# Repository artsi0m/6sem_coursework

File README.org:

* Курсовой шестого семестра
Программное обеспечение моделирования физических процессов,
протекающих в системе тестирования сервоприводов квадрокоптера на микроконтроллере ATmega328P

** Используемые программы

| Программа             | Что в ней было произведено                                         |
| Altium Designer       | Схема электрическая принципиальная, экспорт модели из кикада в IDF |
| KiCAD 8               | Схема электрическая принципальная, модель печатной платы           |
| Solidworks Simulation | Импорт IDF из Altium, физические симуляции и экспорт в STEP        |
| COMSOL, ANSYS         | Физические симуляции                                               |

** Используемые классы [xe]latex

| Класс | Документ                                                          |
| xesel | Перечень элементов                                                |
| eskdx | Класс взятый за основу класса bsuir-std для пояснительной записки |

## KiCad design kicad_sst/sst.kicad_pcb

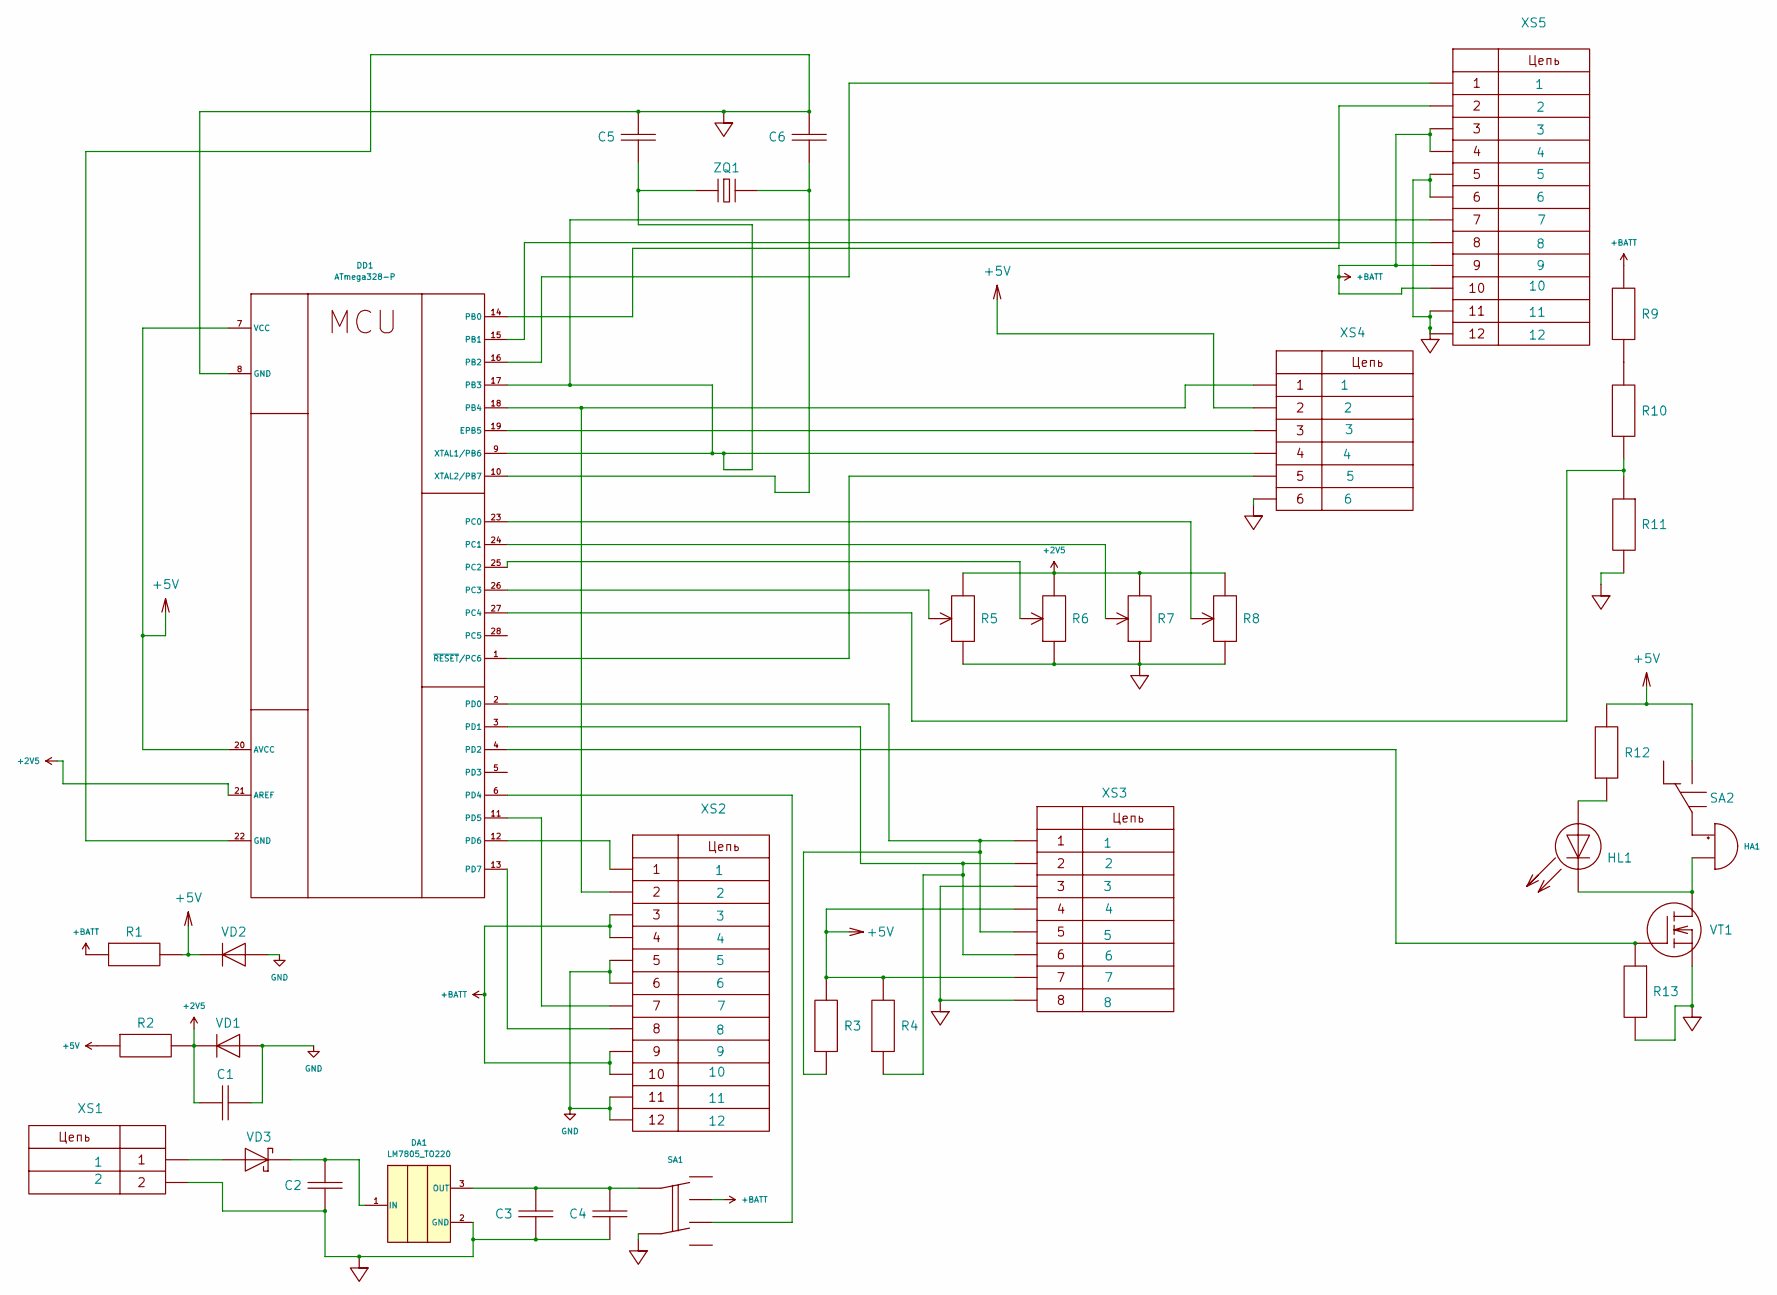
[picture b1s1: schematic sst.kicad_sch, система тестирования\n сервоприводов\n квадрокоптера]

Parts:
C1, C4: C; CP_Radial_D8.0mm_P2.50mm
C2: C; CP_Radial_D8.0mm_P3.50mm
C3: C; CP_Radial_D5.0mm_P2.00mm
C5, C6: C; C_Radial_D6.3mm_H5.0mm_P2.50mm
DA1: LM7805_TO220; TO-220-3_Vertical
DD1: ATmega328-P; DIP-28_W7.62mm
HA1: Buzzer; Buzzer_TDK_PS1240P02BT_D12.2mm_H6.5mm
HL1: HL_LED; LED_D3.0mm
R1, R2, R3, R4, R9, R10, R11, R12, R13: R; R_Axial_DIN0207_L6.3mm_D2.5mm_P7.62mm_Horizontal
R5, R6, R7, R8: R_POT; Potentiometer_TT_P0915N
SA1: SW_CK_JS202011CQN_DPDT_Straight
SA2: SA_SPDT; SW_Slide_SPDT_Angled_CK_OS102011MA1Q
VD1, VD2: VD; D_5KPW_P12.70mm_Horizontal
VD3: VD_Schottky; D_5KPW_P12.70mm_Horizontal
VT1: 2П7240; TO-92
XS1: CONN_2; BarrelJack_SwitchcraftConxall_RAPC10U_Horizontal
XS2, XS5: CONN_12; PinHeader_2x06_P2.54mm_Vertical
XS3: CONN_8; PinSocket_2x04_P2.54mm_Vertical
XS4: CONN_6; PinHeader_2x03_P2.54mm_Vertical
ZQ1: ZQ_CRYSTAL; Crystal_HC49-U_Vertical

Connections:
+2V5: C1.1, DD1.21 (AREF), R2.2, R5.3, R6.3, R7.3, R8.3, VD1.1 (K)
+5V: DD1.7 (VCC), DD1.20 (AVCC), R1.2, R2.1, R3.2, R4.2, R12.2, SA2.2, VD2.1 (K), XS3.4, XS3.7, XS4.2
+BATT: R1.1, R9.2, SA1.4, XS2.3, XS2.4, XS2.9, XS2.10, XS5.3, XS5.4, XS5.9, XS5.10
GND: C1.2, C2.2, C3.2, C4.2, C5.1, C6.1, DA1.2 (GND), DD1.8 (GND), DD1.22 (GND), R5.1, R6.1, R7.1, R8.1, R11.2, R13.2, SA1.2, VD1.2 (A), VD2.2 (A), VT1.1 (S1), XS1.2, XS2.5, XS2.6, XS2.11, XS2.12, XS3.3, XS3.8, XS4.6, XS5.5, XS5.6, XS5.11, XS5.12
unnamed: C2.1, DA1.1 (IN), VD3.1 (K)
unnamed: C3.1, C4.1, DA1.3 (OUT), SA1.1
unnamed: DD1.19 (EPB5), XS4.3
unnamed: DD1.14 (PB0), XS5.2
unnamed: DD1.15 (PB1), XS5.8
unnamed: DD1.16 (PB2), XS5.1
unnamed: C5.2, DD1.9 (XTAL1/PB6), DD1.17 (PB3), XS4.4, XS5.7, ZQ1.1
unnamed: DD1.18 (PB4), XS2.2, XS4.1
unnamed: DD1.23 (PC0), R8.2
unnamed: DD1.24 (PC1), R7.2
unnamed: DD1.25 (PC2), R6.2
unnamed: DD1.26 (PC3), R5.2
unnamed: DD1.27 (PC4), R10.1, R11.1
unnamed: DD1.2 (PD0), R3.1, XS3.1, XS3.5
unnamed: DD1.3 (PD1), R4.1, XS3.2, XS3.6
unnamed: DD1.4 (PD2), R13.1, VT1.2 (G1)
unnamed: DD1.6 (PD4), SA1.5
unnamed: DD1.11 (PD5), XS2.7
unnamed: DD1.12 (PD6), XS2.1
unnamed: DD1.13 (PD7), XS2.8
unnamed: C6.2, DD1.10 (XTAL2/PB7), ZQ1.2
unnamed: DD1.1 (~RESET/PC6), XS4.5
unnamed: HA1.1 (+), SA2.1
unnamed: HA1.2 (-), HL1.1 (K), VT1.3 (D1)
unnamed: HL1.2 (A), R12.1
unnamed: R9.1, R10.2
unnamed: VD3.2 (A), XS1.1

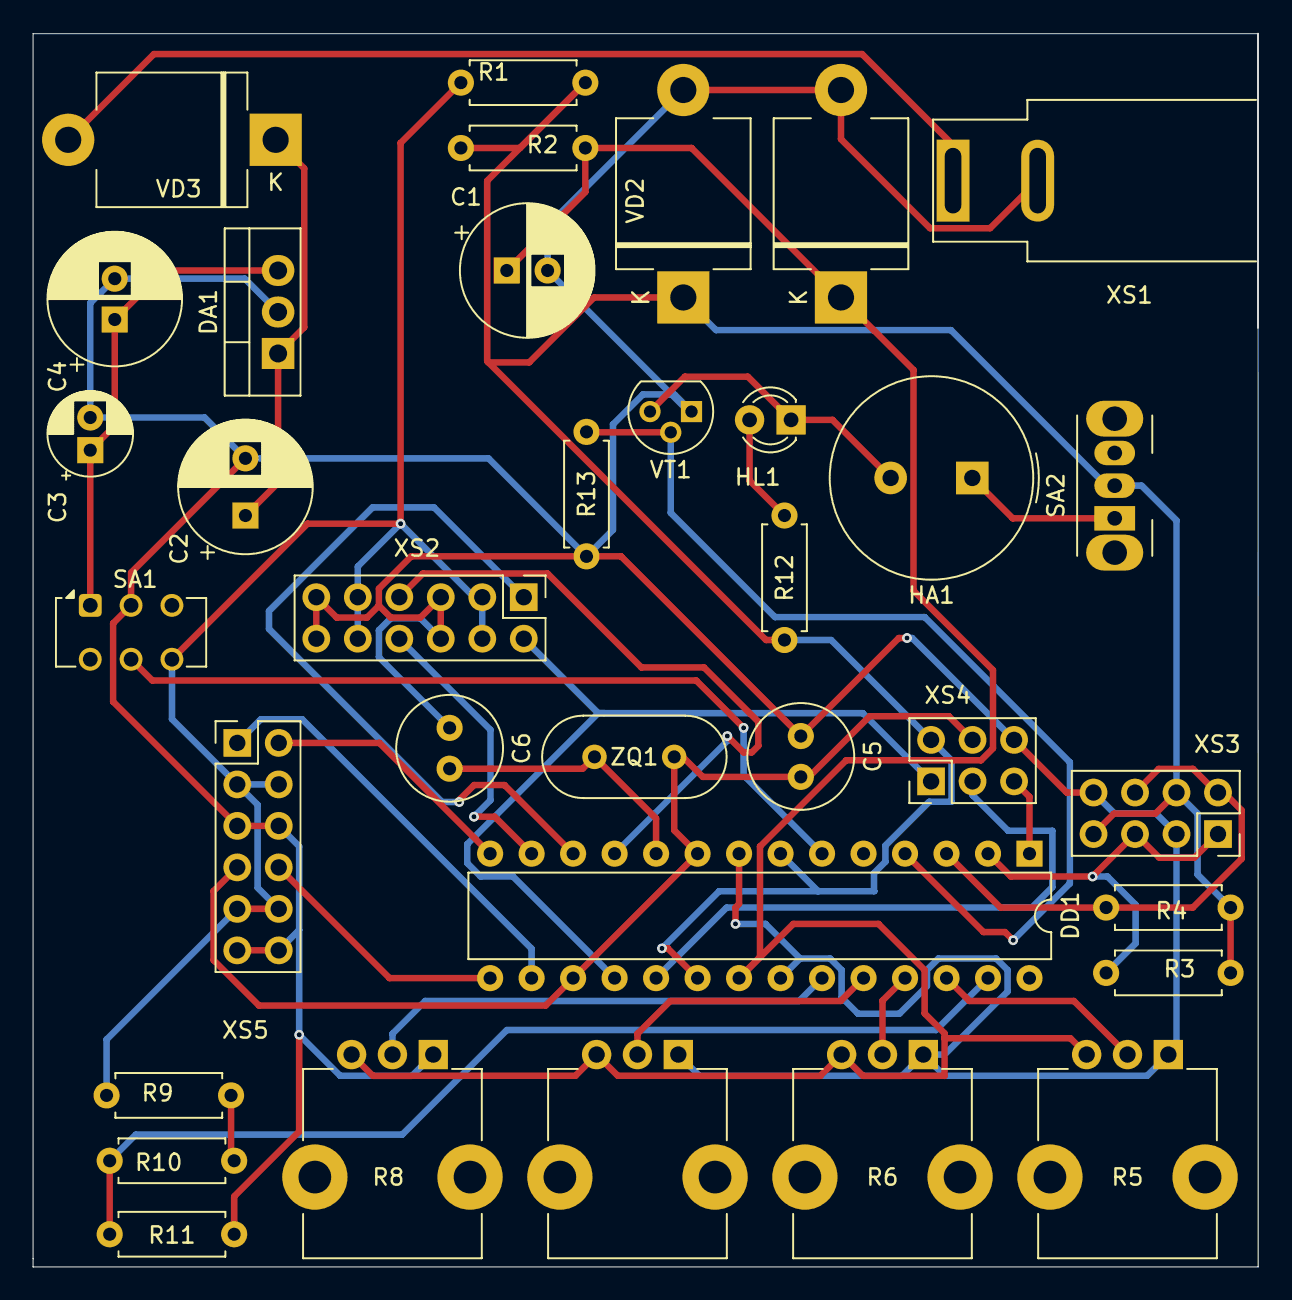
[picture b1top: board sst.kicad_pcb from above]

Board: 2 copper layers, 75.0 x 75.5 mm, 35 parts (0 on the bottom side), 31 nets.

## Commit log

2024-02-29 Первая версия перечня элементов
2024-02-29 Шрифт Open GOST A для чертежей
2024-02-29 README с инфой по используемуму софту
2024-03-01 Мой класс с прошлого курсового
2024-03-01 Начало пояснительной записки, дали 5%
2024-03-15 Initial commit with Altium Project, created schematic lib
2024-03-15 2023-03-15-2115 Readme update
2024-03-15 ЕСКД Класс на схеме электрической принципальной
2024-03-15 SST — Super Servo Tester
2024-03-24 Xtal now has QX designator like in GOST
2024-03-24 Укрупнил микроконтроллер и поменял местами его выводы
2024-03-24 Разместил на схеме микроконтроллер и кварцевый резонатор
2024-03-24 Поставил регулятор напряжения на принципальную схему
2024-03-24 rename ZX to ZQ on Xtal
2024-03-25 Changed LED and MOSFET
2024-03-25 Added connector for 6,8,12 pins
2024-03-25 Updated potentiometr
2024-03-26 All work done on schematics yesterday 2024-03-25
2024-03-26 Placed almost everything on the scheme
2024-03-26 Enumerated all components and changed GND
2024-03-26 Enumerate all elements in project
2024-03-26 Enumerated and connected all
2024-03-26 Fixed connection between XS3 and MCU
2024-03-26 Commit to keep changes in scheme
2024-03-26 Добавил на принципальную схему те части, которые не соеденены с микроконтроллером, пронумеровал всё
2024-03-29 Сменил форму рамки ЕСКд на 2А
2024-03-29 Переместил землю так, чтобы её УГОшка была направлена вниз
2024-03-29 Удалил надпись GND с земли
2024-03-29 Поменял обозначения питания
2024-04-21 Started adding titles to MCU pins
2024-04-24 Created kicad project
2024-04-24 Добавил рамки по госту
2024-04-25 Switched to gost font and set to metric
2024-04-25 Добавил в свою библиотеку из встроенной символ атмеги
2024-04-26 Сделал УГО микроконтроллера по ГОСТ
2024-04-27 Сделал УГО микроконтроллера
2024-04-27 HA УГО
2024-04-27 SA, XS, ZQ added
2024-04-27 Вроде как полная схемная библиотека
2024-04-28 Almsost done with the sceme: part that connected to MCU is connected
2024-04-28 Done with schematic
2024-04-28 Fixes to the schematics
2024-04-28 placed footprints
2024-04-29 Сделлал аннотацию схемы
2024-04-29 Linked footprints to schematics
2024-04-29 Fixes transistor
2024-04-30 Changed couple of footprints for XS
2024-05-01 first try at tracing, and I think I set wrong component at XS4
2024-05-01 Changed footprint for XS4
2024-05-01 version of PCB layout without errors
2024-05-01 pcb without warnings
2024-05-01 Readme Update
2024-05-02 deleted all tracks
2024-05-02 created groups of objects
2024-05-02 fixes to potentiometers on schematics
2024-05-02 Updated pcb according to schematics
2024-05-02 Changed capacitors
2024-05-02 Arranged components on PCB
2024-05-02 Rearranged components a little bit
2024-05-03 Подписал рамки
2024-05-03 Project file I forget about
2024-05-03 Traced everything but power
2024-05-04 traced pcb
2024-05-04 Potentiometer step model
2024-05-04 placed potentiometers step models
2024-05-04 BarellJack step model
2024-05-04 Added barell jack step model
2024-05-04 Exported step file of the first board
2024-05-04 Locked elements that would be constant on PCB
2024-05-04 PCB with resistors, capacitors and barell jack turned to other side
2024-05-04 Вторая компоновка печатной платы в формате step
2024-05-05 Третья версия компоновки ПП с уменьшенными компонентами
2024-05-05 Exported step file of the third board
2024-05-06 Removed step downloaded step files
2024-05-06 Removed some 3d models from first board
2024-05-06 Removed step bad 3d models of boards
2024-05-06 Removed some 3d models from second board
2024-05-06 Removed some 3d models from third board
2024-05-06 Exported step models of PCB's
2024-05-06 Another try to export step models of PCB's
2024-05-08 pcb-s imported in altium
2024-05-08 Imported in Altium kicad sst project
2024-05-08 kicad .kicad_pcb -> Altium .PcbDoc -> IDF export of the boards
2024-05-12 Pictures of simulation studies in solidworks
2024-05-13 STEP models from SOLIDWORKS
2024-05-13 Images from SOLIDWORKS studies
2024-05-13 STEP models from SOLIDWORKS redone
2024-05-14 Продолжая писать записку
2024-05-14 Bibliography from Zotero
2024-05-15 Первые два подраздела пояснительной записки
2024-05-15 Writing chapter 2
2024-05-16 Almost all done, but problem with images
2024-05-16 Fixed images and tables wit usepackage float
2024-05-16 Seems to be final version
2024-05-16 Images for coursework
